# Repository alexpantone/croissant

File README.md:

# Croissant Breadboard Prototyping Tool
The Croissant is a multi-function PCB that lets you use your existing synthesizer equipment with a standard breadboard, with plenty of addons and extras.
Check out the video! [https://youtu.be/_RGXiyb1UPI?si=hu-ymMrpfnG7xpGm]

One day, I was using a breadboard to test out a circuit design for my synthesizer, and I was trying to hold a headphone jack and a power connector with its cable onto the board with one hand, and another headphone jack with another hand, all while trying to turn a knob on the synth. That made me think there had to be a better way to get synthesizer components onto a breadboard, so I make just such a tool. It's shaped like a C and it goes on a breadboard, so I called it the Croissant.

The primary feature is a combined footprint for Pocket Rack (Molex SL) and Eurorack (5x2 pin shrouds) power connectors that routes +12v, Ground, and -12v to the power rails of a breadboard via pin headers. This lets you use your existing equipment on a breadboard and power it with the actual synth you will eventually use your designs in.

## Configurations
### Minimal
To use the Croissant in its most basic mode, all you need to do is add a power connector of your choice, jump the two pads labeled "0 Ohm Bypass", and install a power switch or jump the pins.

### Reverse Polarity
Alternatively, you can add the capacitors and diodes for reverse polarity protection and NOT jump the 0 Ohm Bypass to guarantee your +12v and -12v lines are always just that.

### Peripherals
In addition, the Croissant has two slots that can each fit either a vertical 3.5mm stereo jack, a horizontal jack, or a potentiometer. These connections are routed to the breadboard as well, both on the inside where the power is attached, but also on the edge of the Croissant so you can use more than one of them at a time on your breadboard.

### 3.3v and 5v Lines
There are also two footprints for adding two linear regulators (through-hole or surface-mount in the same footprint) and their associated capacitors. The board is labeled for 3.3v and 5v for microcontrollers such as a Raspberry Pi Pico or an Arduino.

### Amp
Also, since the price at most PCB fabs is the same either way, I added a small audio amplifier board to the middle of the Croissant that you can snap out. I designed it around an FM8002A based on this video: https://www.youtube.com/watch?v=I4WP1u4hwpw
I haven't tried this out myself yet, so I can't confirm if it works. I hope to soon once the parts come in. The datasheet recommended tying the positive input pin to ground and connecting the audio in to the negative input, but that sounded odd to me even if this is exclusively supposed to be an inverting amplifier. I made a footprint pattern with 0 Ohm resistors in a square where if they are soldered as the silkscreen indicates, they will produce this configuration. If these resistors are both rotate 90 degrees, that will route the audio in to the positive input of the FM8002A and tie the negative input to ground.

I only started learning PCB design a few months ago, so I'm always open to suggestions and improvements!

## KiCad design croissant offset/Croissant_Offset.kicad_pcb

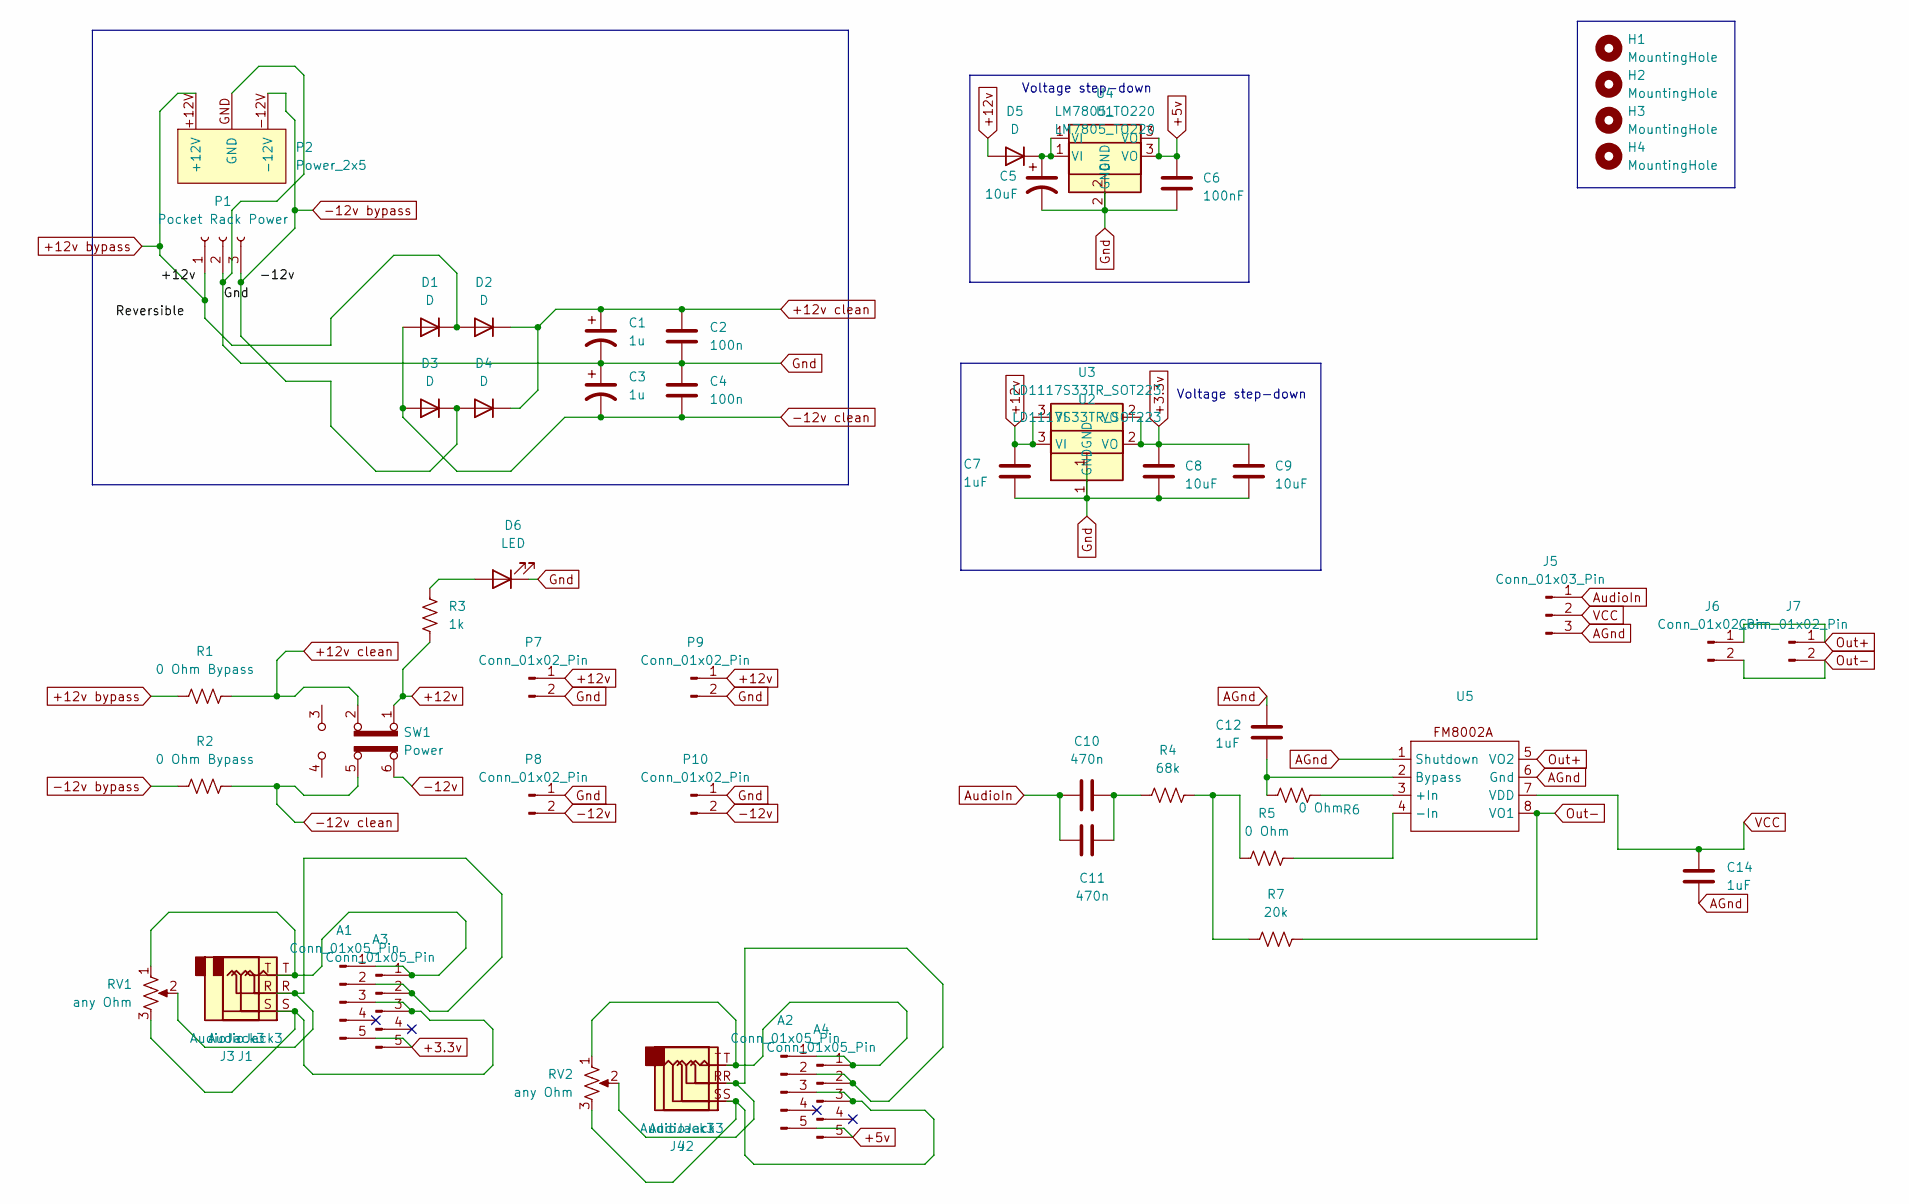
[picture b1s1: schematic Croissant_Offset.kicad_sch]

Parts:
A1, A2, A3, A4: Conn_01x05_Pin; PinHeader_1x05_P2.54mm_Vertical
C1, C3: 1u; CP_EIA-3216-10_Kemet-I_Pad1.58x1.35mm_HandSolder
C2, C4: 100n; C_0805_2012Metric_Pad1.18x1.45mm_HandSolder
C5, C8, C9: 10uF; C_0805_2012Metric_Pad1.18x1.45mm_HandSolder
C6: 100nF; C_0805_2012Metric_Pad1.18x1.45mm_HandSolder
C7, C12, C14: 1uF; C_0805_2012Metric_Pad1.18x1.45mm_HandSolder
C10, C11: 470n; C_0805_2012Metric_Pad1.18x1.45mm_HandSolder
D1, D2, D3, D4, D5: D; D_0805_2012Metric_Pad1.15x1.40mm_HandSolder
D6: LED; LED_D3.0mm
H1, H2, H3, H4: MountingHole; MountingHole_2.2mm_M2
J1, J2: AudioJack3; Jack_3.5mm_TRS_Horizontal
J3, J4: AudioJack3; Jack_3.5mm_QingPu_WQP-PJ301CM
J5: Conn_01x03_Pin; PinHeader_1x03_P2.54mm_Vertical
J6: Conn_01x02_Pin; PinHeader_1x02_P2.54mm_Vertical
J7: Conn_01x02_Pin; TerminalBlock_4Ucon_1x02_P3.50mm_Horizontal
P1: Pocket Rack Power; Molex_SL_171971-0003_1x03_P2.54mm_Vertical
P2: Power_2x5; Power_2x5_Vertical
P7, P8, P9, P10: Conn_01x02_Pin; PinHeader_1x02_P2.54mm_Vertical
R1, R2: 0 Ohm Bypass; R_0805_2012Metric_Pad1.20x1.40mm_HandSolder
R3: 1k; R_0805_2012Metric_Pad1.20x1.40mm_HandSolder
R4: 68k; R_0805_2012Metric_Pad1.20x1.40mm_HandSolder
R5, R6: 0 Ohm; R_0805_2012Metric_Pad1.20x1.40mm_HandSolder
R7: 20k; R_0805_2012Metric_Pad1.20x1.40mm_HandSolder
RV1, RV2: any Ohm; Potentiometer_Vertical_Slimmer
SW1: Power; SW_CK_JS202011CQN_DPDT_Straight
U1: LM7805_TO220; TO-220-3_Vertical
U2: LD1117S33TR_SOT223; TO-220-3_Vertical
U3: LD1117S33TR_SOT223; SOT-223-3_TabPin2
U4: LM7805_TO220; SOT-223-3_TabPin2
U5: SOP-8_3.9x4.9mm_P1.27mm

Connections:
+3.3v: A1.5, A3.5, C8.1, C9.1, U2.2 (VO), U3.2 (VO)
+5v: A2.5, A4.5, C6.1, U1.3 (VO), U4.3 (VO)
+12v: C7.1, D5.2 (A), P7.1, P9.1, R3.2, SW1.1 (A), U2.3 (VI), U3.3 (VI)
+12v bypass: D1.1 (K), D2.2 (A), P1.1, P2.+12V, R1.1
+12v clean: C1.1, C2.1, D2.1 (K), D4.1 (K), R1.2, SW1.2 (B)
-12v: P8.2, P10.2, SW1.6 (C)
-12v bypass: D3.1 (K), D4.2 (A), P1.3, P2.-12V, R2.1
-12v clean: C3.2, C4.2, D1.2 (A), D3.2 (A), R2.2, SW1.5 (B)
AGnd: C12.1, C14.2, J5.3, U5.1 (Shutdown), U5.6 (Gnd)
AudioIn: C10.1, C11.1, J5.1
Gnd: C1.2, C2.2, C3.1, C4.1, C5.2, C6.2, C7.2, C8.2, C9.2, D6.1 (K), P1.2, P2.GND, P7.2, P8.1, P9.2, P10.1, U1.2 (GND), U2.1 (GND), U3.1 (GND), U4.2 (GND)
unnamed: A1.1, A3.1, J1.T, J3.T, RV1.1
unnamed: A1.2, A3.2, J1.R, J3.R, RV1.2
unnamed: A1.3, A3.3, J1.S, J3.S, RV1.3
unnamed: A2.1, A4.1, J2.T, J4.T, RV2.1
unnamed: A2.2, A4.2, J2.R, J4.R, RV2.2
unnamed: A2.3, A4.3, J2.S, J4.S, RV2.3
unnamed: C10.2, C11.2, R4.1
unnamed: C5.1, D5.1 (K), U1.1 (VI), U4.1 (VI)
unnamed: D6.2 (A), R3.1
unnamed: R4.2, R5.1, R7.1
unnamed: R6.1, U5.3 (+In)
unnamed: R5.2, U5.4 (-In)
unnamed: C12.2, R6.2, U5.2 (Bypass)
Out+: J6.1, J7.1, U5.5 (VO2)
Out-: J6.2, J7.2, R7.2, U5.8 (VO1)
VCC: C14.1, J5.2, U5.7 (VDD)

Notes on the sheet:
Voltage step-down

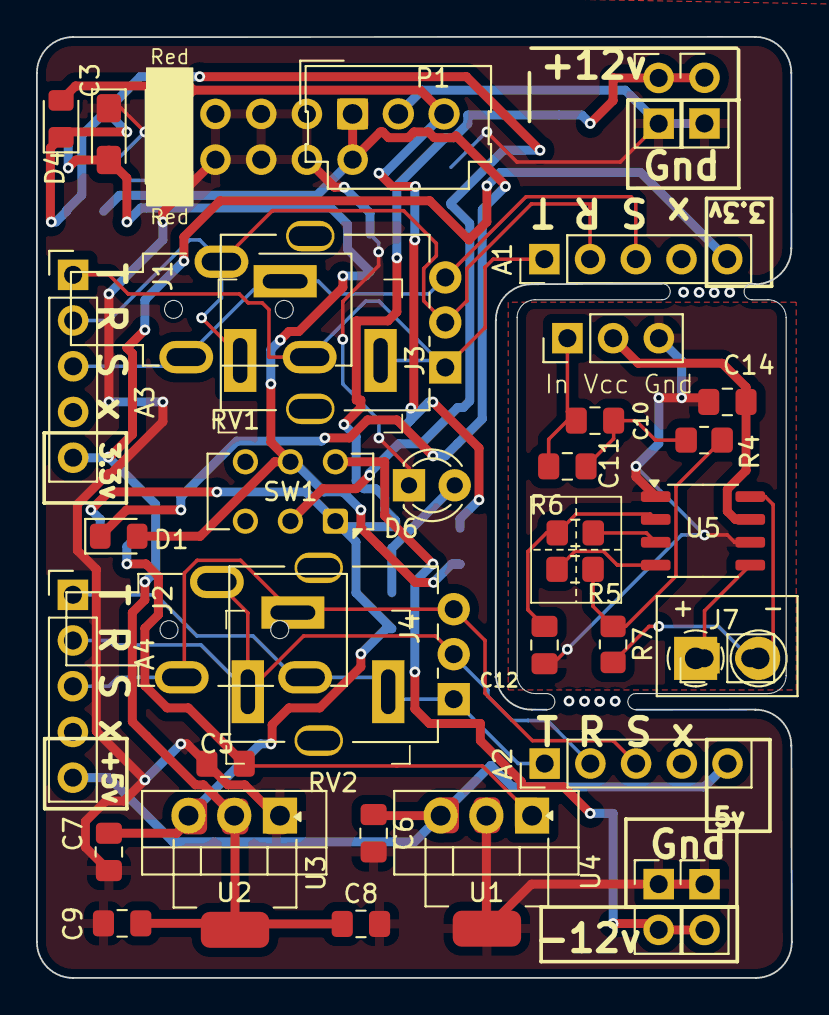
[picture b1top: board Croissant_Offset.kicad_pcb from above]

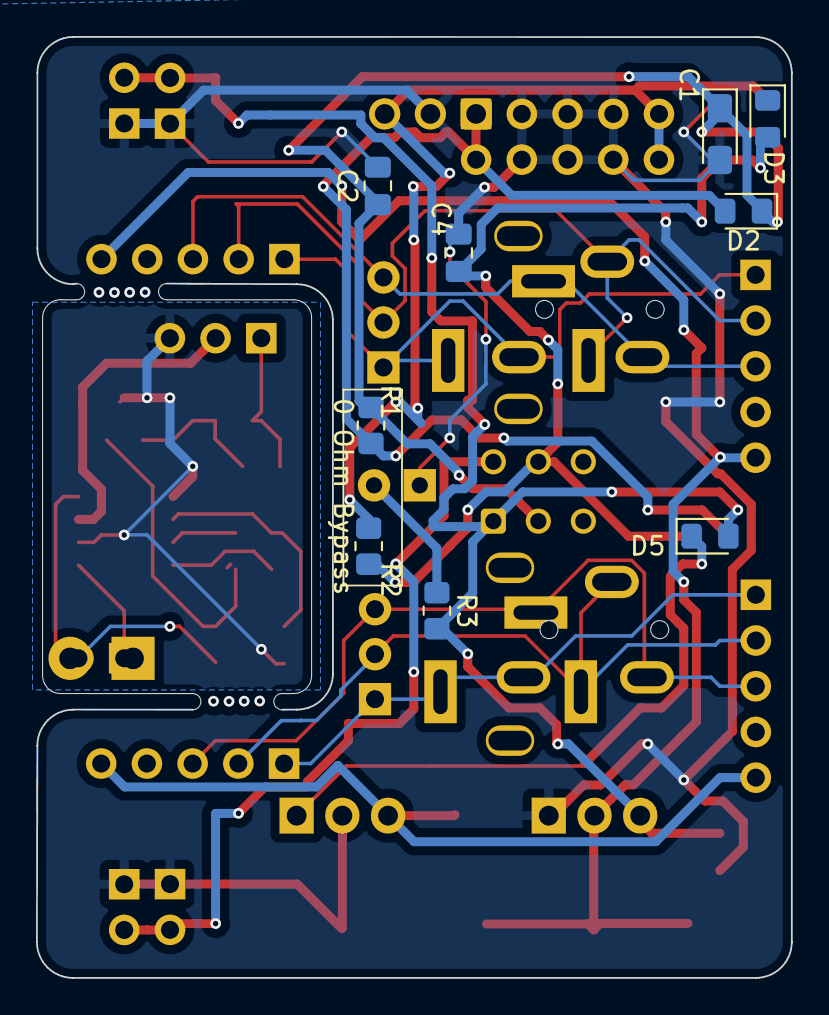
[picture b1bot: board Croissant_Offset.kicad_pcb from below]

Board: 2 copper layers, 41.9 x 52.3 mm, 51 parts (9 on the bottom side), 27 nets.

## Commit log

2024-08-26 Create License
    CERN Open Hardware Licence Version 2 - Permissive (CERN-OHL-P-2.0)
2024-08-26 Add files via upload
    Added KiCad and Gerber files for standard breadboard
2024-08-26 Add files via upload
    Added KiCad and gerber files for a protoboard, which is a different spacing than a breadboard.
2024-08-26 Add files via upload
    KiCad and gerber files for breadboards where the power rails are offset laterally from the main body rails by one-half a pin pitch (.05").
2024-09-22 Added BOM
2024-09-22 Added render of PCB
2024-09-22 Update README.md
    Added inline image
2024-09-23 Update Croissant.csv
    Accidentally repeatedC10 and C11 in 3.3v section
2024-09-23 Added image guides
2024-09-23 Update README.md
    Added photos, improved formatting
